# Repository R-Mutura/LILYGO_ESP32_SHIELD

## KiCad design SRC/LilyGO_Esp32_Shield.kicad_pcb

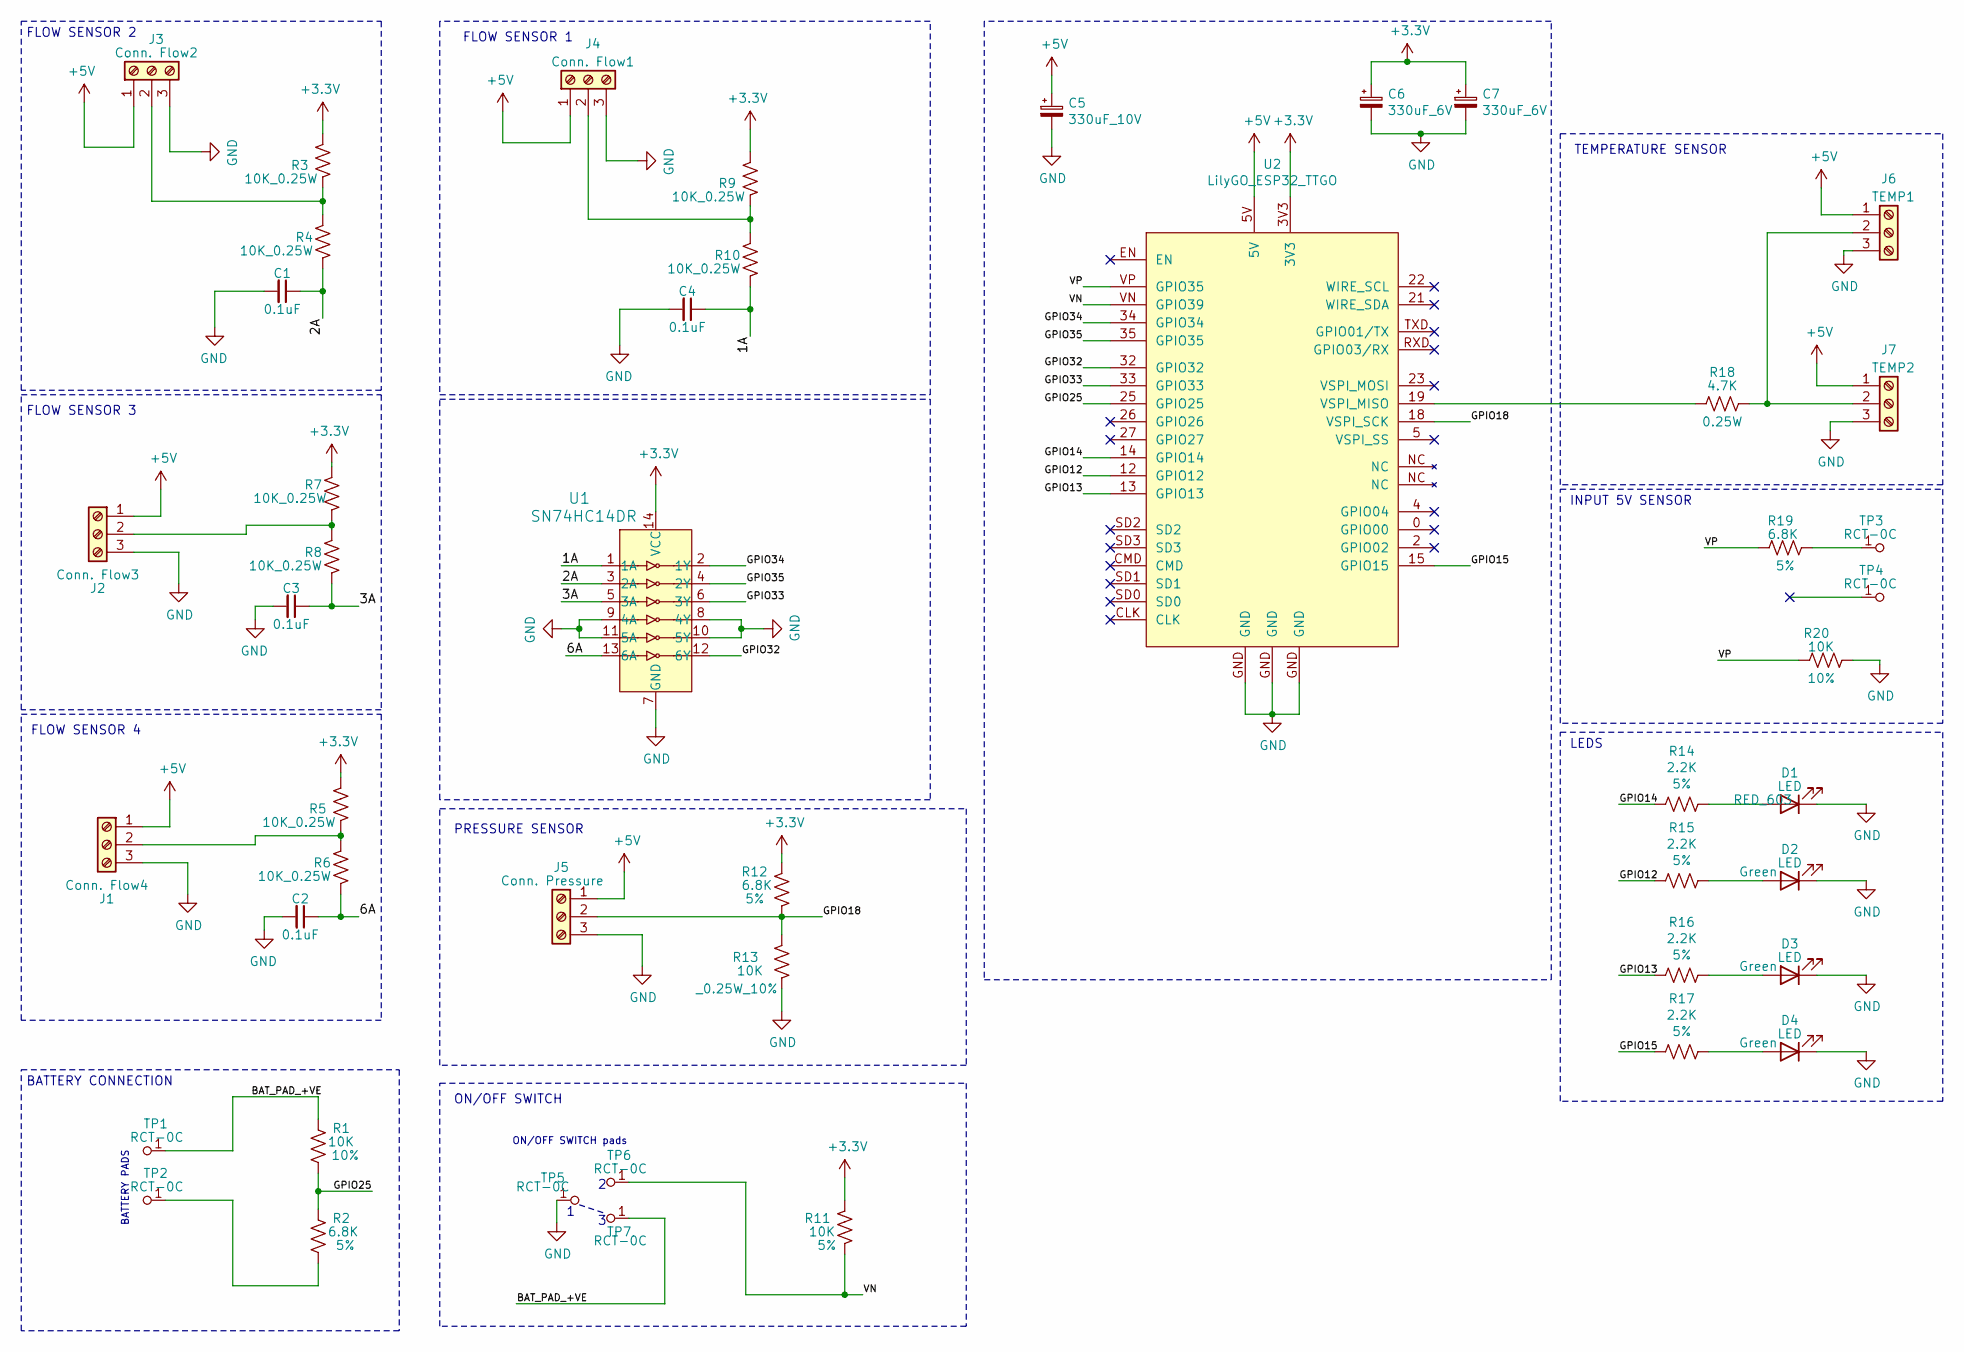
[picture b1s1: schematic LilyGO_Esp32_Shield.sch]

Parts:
C1, C2, C3, C4: 0.1uF; C_0603_1608Metric; MPN GMC10X7R104K50NT
C5: 330uF_10V; CP_Elec_8x10.5
C6, C7: 330uF_6V; CP_Elec_6.3x7.7
D1: LED; LED_0603_1608Metric; MPN LTST-C191KRKT
D2, D3, D4: LED; LED_0603_1608Metric; MPN 5988070107F
J1: Conn. Flow4; PhoenixContact_MCV_1,5_3-G-3.5_1x03_P3.50mm_Vertical; MPN 0532590329
J2: Conn. Flow3; PhoenixContact_MCV_1,5_3-G-3.5_1x03_P3.50mm_Vertical; MPN 0532590329
J3: Conn. Flow2; PhoenixContact_MCV_1,5_3-G-3.5_1x03_P3.50mm_Vertical; MPN 0532590329
J4: Conn. Flow1; PhoenixContact_MCV_1,5_3-G-3.5_1x03_P3.50mm_Vertical; MPN 0532590329
J5: Conn. Pressure; PhoenixContact_MCV_1,5_3-G-3.5_1x03_P3.50mm_Vertical; MPN 0532590329
J6: TEMP1; PhoenixContact_MCV_1,5_3-G-3.5_1x03_P3.50mm_Vertical; MPN 0532590329
J7: TEMP2; PhoenixContact_MCV_1,5_3-G-3.5_1x03_P3.50mm_Vertical; MPN 0532590329
R1, R11, R13, R20: 10K; R_0603_1608Metric; MPN 0603WAF1002T5E
R2, R12, R19: 6.8K; R_0603_1608Metric; MPN RMCF0603JT6K80
R3, R4, R5, R6, R7, R8, R9, R10: 10K_0.25W; R_0603_1608Metric; MPN ESR03EZPJ103
R14, R15, R16, R17: 2.2K; R_0603_1608Metric; MPN 0603WAJ0222T5E
R18: 4.7K; R_0603_1608Metric; MPN ERJPA3F4701V
TP1, TP2, TP3, TP4, TP5, TP6, TP7: RCT-0C; PROBE_PAD_1206; MPN RCT-0C; Digi-Key_PN A106144CT-ND
U1: SN74HC14DR; SOIC-14_3.9x8.7mm_P1.27mm; MPN SN74HC14DR; Digi-Key_PN 296-1577-5-ND
U2: LilyGO_ESP32_TTGO; LILLYGO_ESP32_TTGO

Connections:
+3V3: C6.1, C7.1, R3.1, R5.1, R7.1, R9.1, R11.1, R12.1, U1.14 (VCC), U2.3V3
+5V: C5.1, J1.1, J2.1, J3.1, J4.1, J5.1, J6.1, J7.1, U2.5V
/1A: C4.1, R10.2, U1.1 (1A)
/2A: C1.1, R4.2, U1.3 (2A)
/3A: C3.1, R8.2, U1.5 (3A)
/6A: C2.1, R6.2, U1.13 (6A)
/BAT_PAD_+VE: R1.1, TP1.1, TP7.1
/GPIO12: R15.2, U2.12 (GPIO12)
/GPIO13: R16.2, U2.13 (GPIO13)
/GPIO14: R14.2, U2.14 (GPIO14)
/GPIO15: R17.2, U2.15 (GPIO15)
/GPIO18: J5.2, R12.2, R13.1, U2.18 (VSPI_SCK)
/GPIO25: R1.2, R2.1, U2.25 (GPIO25)
/GPIO32: U1.12 (6Y), U2.32 (GPIO32)
/GPIO33: U1.6 (3Y), U2.33 (GPIO33)
/GPIO34: U1.2 (1Y), U2.34 (GPIO34)
/GPIO35: U1.4 (2Y), U2.35 (GPIO35)
/VN: R11.2, TP6.1, U2.VN (GPIO39)
/VP: R19.1, R20.1, U2.VP (GPIO35)
GND: C1.2, C2.2, C3.2, C4.2, C5.2, C6.2, C7.2, D1.1 (K), D2.1 (K), D3.1 (K), D4.1 (K), J1.3, J2.3, J3.3, J4.3, J5.3, J6.3, J7.3, R13.2, R20.2, TP5.1, U1.7 (GND), U1.8 (4Y), U1.9 (4A), U1.10 (5Y), U1.11 (5A), U2.GND
unnamed: D1.2 (A), R14.1
unnamed: D2.2 (A), R15.1
unnamed: D3.2 (A), R16.1
unnamed: D4.2 (A), R17.1
unnamed: J1.2, R5.2, R6.1
unnamed: J2.2, R7.2, R8.1
unnamed: J3.2, R3.2, R4.1
unnamed: J4.2, R9.2, R10.1
unnamed: J6.2, J7.2, R18.1
unnamed: R2.2, TP2.1
unnamed: R18.2, U2.19 (VSPI_MISO)
unnamed: R19.2, TP3.1

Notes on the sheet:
BATTERY PADS
ON/OFF SWITCH pads
FLOW SENSOR 1
FLOW SENSOR 2
FLOW SENSOR 3
FLOW SENSOR 4
PRESSURE SENSOR
BATTERY CONNECTION
ON/OFF SWITCH
TEMPERATURE SENSOR
INPUT 5V SENSOR
LEDS

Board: 2 copper layers, 47 parts (0 on the bottom side), 32 nets, no tracks yet.

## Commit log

2021-11-18 lily go footprint add
2021-11-18 lilly go shield complete
